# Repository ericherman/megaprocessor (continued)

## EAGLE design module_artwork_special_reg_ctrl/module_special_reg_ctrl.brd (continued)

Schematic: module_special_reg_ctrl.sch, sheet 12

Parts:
CMP27, CMP50: 3OR
CMP28: 4X2AND_OR

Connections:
NEXT_WR_DATA_MUX_PC_RA_MSB__7: CMP27.OUT_M (N), CMP28.P$1 (A0)
NEXT_WR_DATA_MUX_PC_RN_MSB: CMP28.OUT_P; also elsewhere on the board
NEXT_WR_DATA_MUX_PS: CMP27.P$3 (2); also elsewhere on the board
OPCODE_IS_PUSH_RA: CMP27.P$1 (0), CMP28.P$3 (B0); also elsewhere on the board
OPCODE_IS_TRAP_JSR_X: CMP28.P$8 (D1); also elsewhere on the board
SIZE_BIT_IS_BYTE: CMP27.P$2 (1); also elsewhere on the board
STATE_0: CMP28.P$4 (B1), CMP28.P$7 (D0); also elsewhere on the board
STATE_6: CMP50.P$1 (0); also elsewhere on the board
STATE_7: CMP50.P$2 (1); also elsewhere on the board
STATE_9: CMP50.P$3 (2); also elsewhere on the board
STATE_15: CMP28.P$5 (C0), CMP28.P$6 (C1); also elsewhere on the board
WE: CMP50.OUT_P
WILL_BE_STATE_7: CMP28.P$2 (A1); also elsewhere on the board

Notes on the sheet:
next_wr_data_mux_pc_rn_msb__7 = ~Cpnt_3OR(next_wr_data_mux_ps, bus_decode_special_reg_2.size_bit_is_byte, bus_decode_special_reg_1.opcode_is_push_ra);
next_wr_data_mux_pc_rn_msb = Cpnt_4x2AND_OR(opcode_is_trap_jsr_x, bus_state[0], bus_state[15], bus_state[15], bus_state[0], bus_decode_special_reg_1.opcode_is_push_ra, bus_decode_special_reg_2.will_be_7, next_wr_data_mux_pc_rn_msb__7);

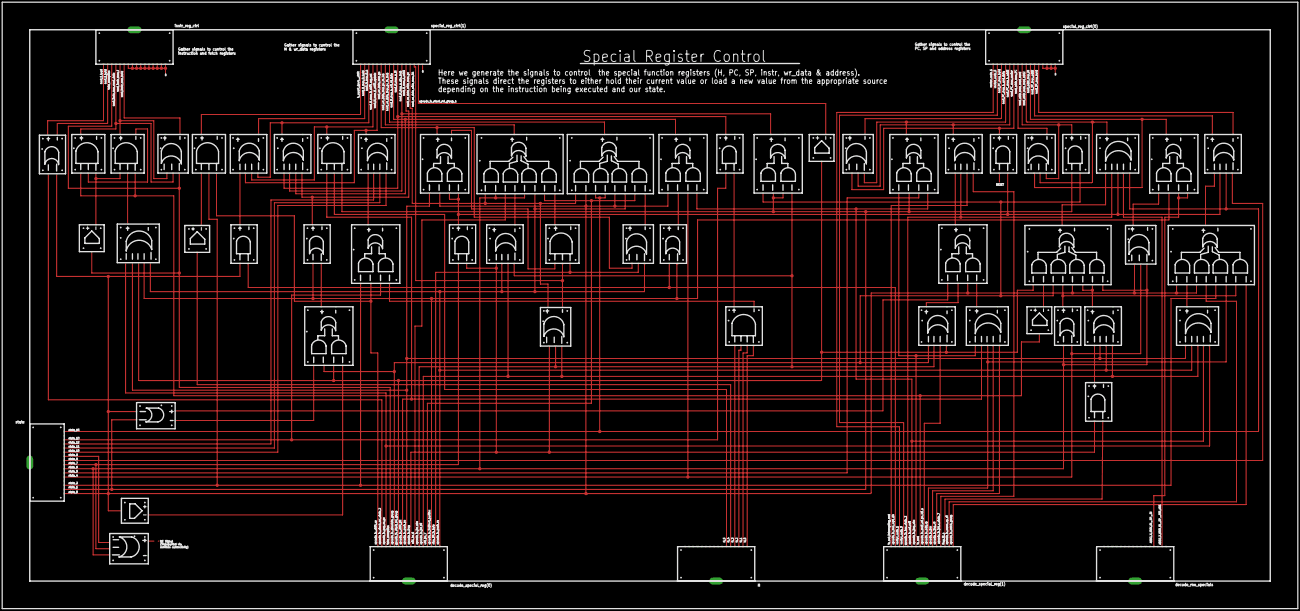
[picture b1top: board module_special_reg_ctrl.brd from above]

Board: 2 copper layers, 1193.8 x 558.8 mm, 61 parts (0 on the bottom side), 115 nets.

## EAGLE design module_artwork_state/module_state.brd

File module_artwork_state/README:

State Machine

The state machine controls the operation of the processor; directing the
execution of each instruction.

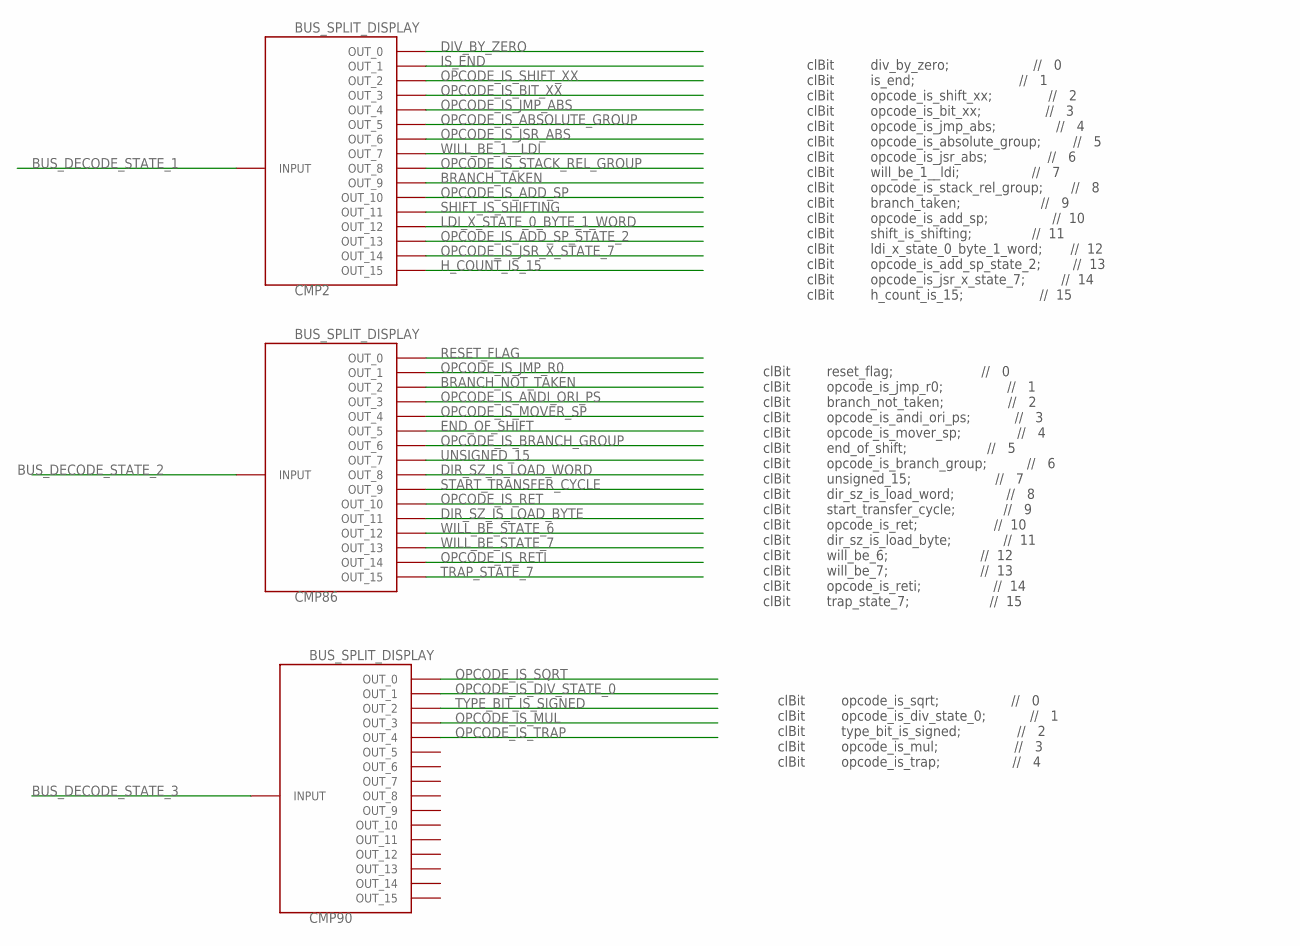
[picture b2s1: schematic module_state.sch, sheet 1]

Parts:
CMP2, CMP86, CMP90: BUS_SPLIT_DISPLAY

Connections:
BRANCH_NOT_TAKEN: CMP86.P$3 (OUT_2); also elsewhere on the board
BRANCH_TAKEN: CMP2.P$10 (OUT_9); also elsewhere on the board
BUS_DECODE_STATE_1: CMP2.INPUT
BUS_DECODE_STATE_2: CMP86.INPUT
BUS_DECODE_STATE_3: CMP90.INPUT
DIR_SZ_IS_LOAD_BYTE: CMP86.P$12 (OUT_11); also elsewhere on the board
DIR_SZ_IS_LOAD_WORD: CMP86.P$9 (OUT_8); also elsewhere on the board
DIV_BY_ZERO: CMP2.P$1 (OUT_0); also elsewhere on the board
END_OF_SHIFT: CMP86.P$6 (OUT_5); also elsewhere on the board
H_COUNT_IS_15: CMP2.P$16 (OUT_15); also elsewhere on the board
IS_END: CMP2.P$2 (OUT_1); also elsewhere on the board
LDI_X_STATE_0_BYTE_1_WORD: CMP2.P$13 (OUT_12); also elsewhere on the board
OPCODE_IS_ABSOLUTE_GROUP: CMP2.P$6 (OUT_5); also elsewhere on the board
OPCODE_IS_ADD_SP: CMP2.P$11 (OUT_10); also elsewhere on the board
OPCODE_IS_ADD_SP_STATE_2: CMP2.P$14 (OUT_13); also elsewhere on the board
OPCODE_IS_ANDI_ORI_PS: CMP86.P$4 (OUT_3); also elsewhere on the board
OPCODE_IS_BIT_XX: CMP2.P$4 (OUT_3); also elsewhere on the board
OPCODE_IS_BRANCH_GROUP: CMP86.P$7 (OUT_6); also elsewhere on the board
OPCODE_IS_DIV_STATE_0: CMP90.P$2 (OUT_1); also elsewhere on the board
OPCODE_IS_JMP_ABS: CMP2.P$5 (OUT_4); also elsewhere on the board
OPCODE_IS_JMP_R0: CMP86.P$2 (OUT_1); also elsewhere on the board
OPCODE_IS_JSR_ABS: CMP2.P$7 (OUT_6); also elsewhere on the board
OPCODE_IS_JSR_X_STATE_7: CMP2.P$15 (OUT_14); also elsewhere on the board
OPCODE_IS_MOVER_SP: CMP86.P$5 (OUT_4); also elsewhere on the board
OPCODE_IS_MUL: CMP90.P$4 (OUT_3); also elsewhere on the board
OPCODE_IS_RET: CMP86.P$11 (OUT_10); also elsewhere on the board
OPCODE_IS_RETI: CMP86.P$15 (OUT_14); also elsewhere on the board
OPCODE_IS_SHIFT_XX: CMP2.P$3 (OUT_2); also elsewhere on the board
OPCODE_IS_SQRT: CMP90.P$1 (OUT_0); also elsewhere on the board
OPCODE_IS_STACK_REL_GROUP: CMP2.P$9 (OUT_8); also elsewhere on the board
OPCODE_IS_TRAP: CMP90.P$5 (OUT_4); also elsewhere on the board
RESET_FLAG: CMP86.P$1 (OUT_0); also elsewhere on the board
SHIFT_IS_SHIFTING: CMP2.P$12 (OUT_11); also elsewhere on the board
START_TRANSFER_CYCLE: CMP86.P$10 (OUT_9); also elsewhere on the board
TRAP_STATE_7: CMP86.P$16 (OUT_15); also elsewhere on the board
TYPE_BIT_IS_SIGNED: CMP90.P$3 (OUT_2); also elsewhere on the board
UNSIGNED_15: CMP86.P$8 (OUT_7); also elsewhere on the board
WILL_BE_1__LDI: CMP2.P$8 (OUT_7); also elsewhere on the board
WILL_BE_STATE_6: CMP86.P$13 (OUT_12); also elsewhere on the board
WILL_BE_STATE_7: CMP86.P$14 (OUT_13); also elsewhere on the board

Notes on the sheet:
clBit div_by_zero; // 0 clBit is_end; // 1 clBit opcode_is_shift_xx; // 2 clBit opcode_is_bit_xx; // 3 clBit opcode_is_jmp_abs; // 4 clBit opcode_is_absolute_group; // 5 clBit opcode_is_jsr_abs; // 6 clBit will_be_1__ldi; // 7 clBit opcode_is_stack_rel_group; // 8 clBit branch_taken; // 9 clBit opc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
clBit reset_flag; // 0 clBit opcode_is_jmp_r0; // 1 clBit branch_not_taken; // 2 clBit opcode_is_andi_ori_ps; // 3 clBit opcode_is_mover_sp; // 4 clBit end_of_shift; // 5 clBit opcode_is_branch_group; // 6 clBit unsigned_15; // 7 clBit dir_sz_is_load_word; // 8 clBit start_transfer_cycle; // 9 clBi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
clBit opcode_is_sqrt; // 0 clBit opcode_is_div_state_0; // 1 clBit type_bit_is_signed; // 2 clBit opcode_is_mul; // 3 clBit opcode_is_trap; // 4

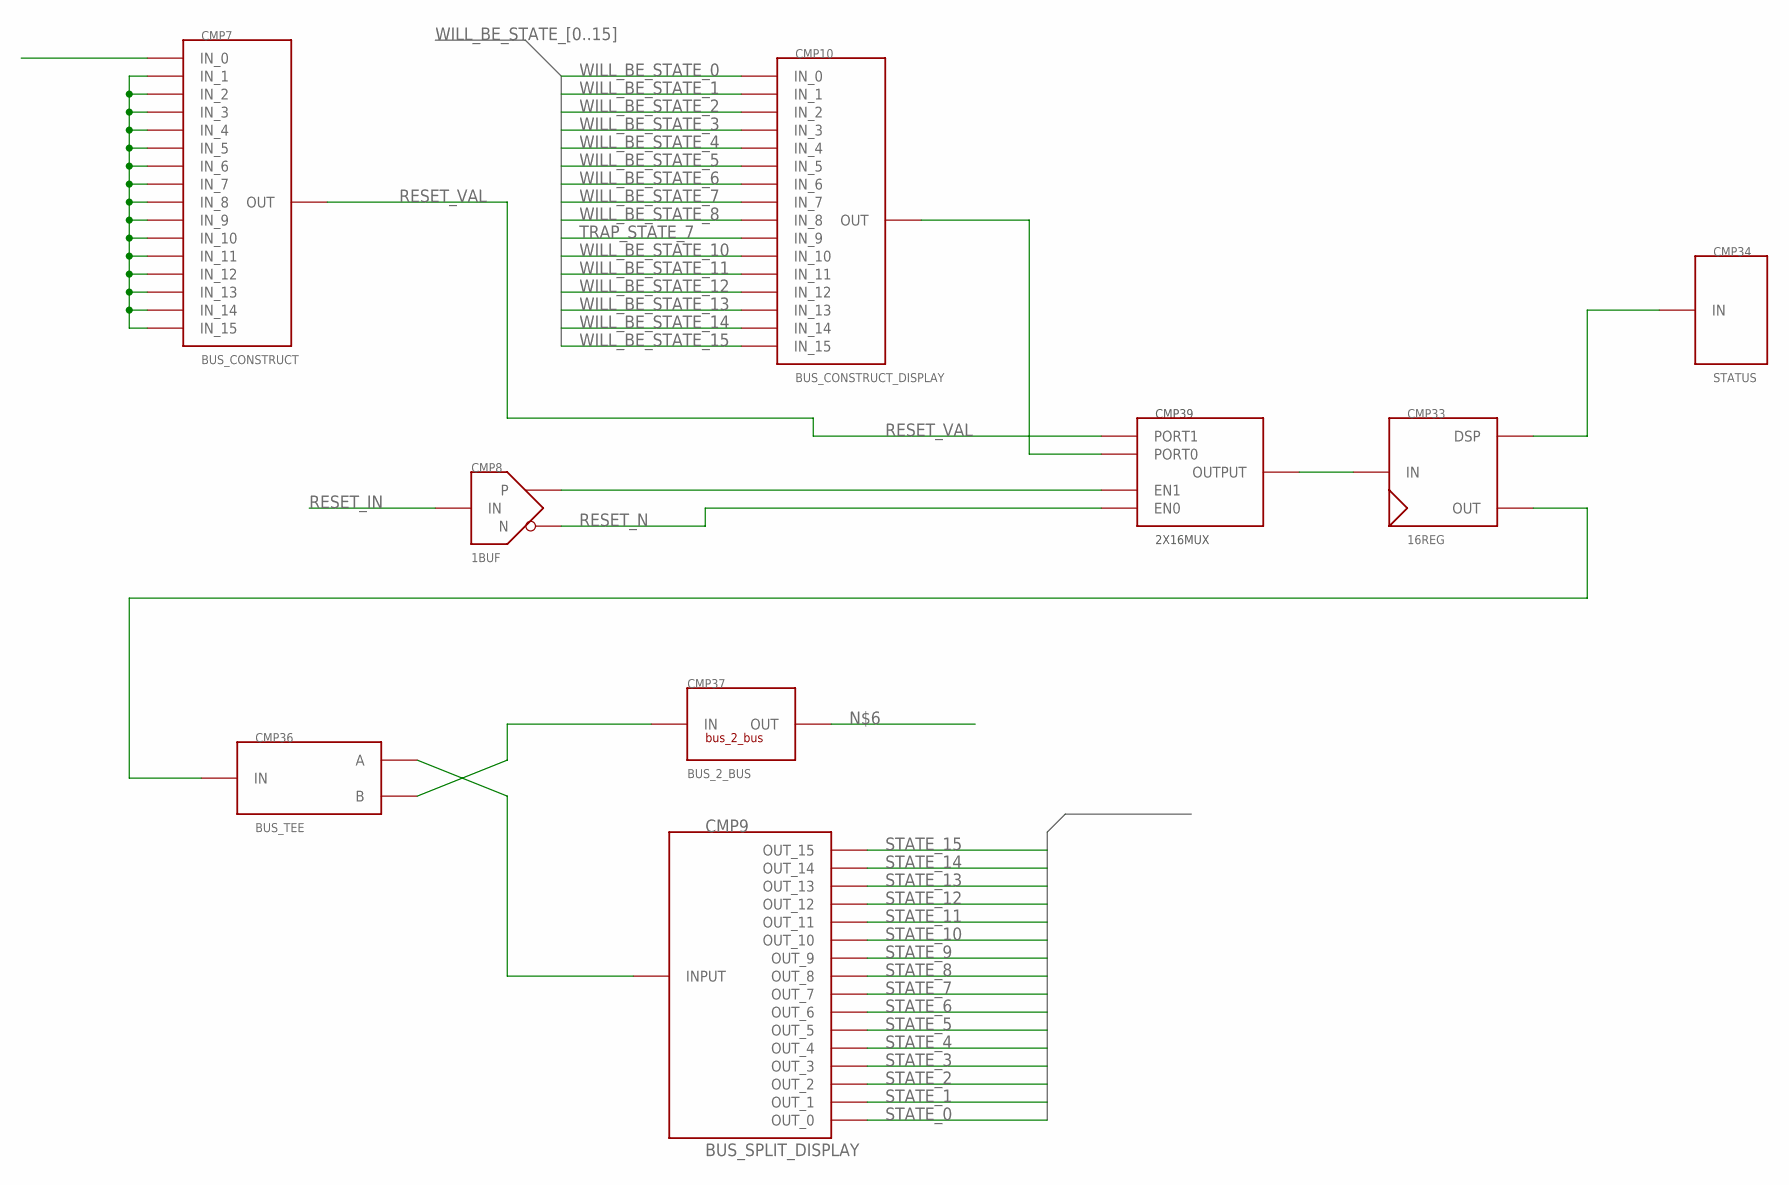
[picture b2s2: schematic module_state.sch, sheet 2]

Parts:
CMP7: BUS_CONSTRUCT; BUS_SPLIT
CMP8: 1BUF
CMP9: BUS_SPLIT_DISPLAY
CMP10: BUS_CONSTRUCT_DISPLAY; BUS_SPLIT_DISPLAY
CMP33: 16REG
CMP34: STATUS
CMP36: BUS_TEE
CMP37: BUS_2_BUS; BUS2BUS
CMP39: 2X16MUX

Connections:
unnamed: CMP33.DISPLAY (DSP), CMP34.P$1
unnamed: CMP33.OUT, CMP36.INPUT (IN)
unnamed: CMP36.OUTB (B), CMP37.P$1 (IN)
unnamed: CMP7.P$2 (IN_1), CMP7.P$3 (IN_2), CMP7.P$4 (IN_3), CMP7.P$5 (IN_4), CMP7.P$6 (IN_5), CMP7.P$7 (IN_6), CMP7.P$8 (IN_7), CMP7.P$9 (IN_8), CMP7.P$10 (IN_9), CMP7.P$11 (IN_10), CMP7.P$12 (IN_11), CMP7.P$13 (IN_12), CMP7.P$14 (IN_13), CMP7.P$15 (IN_14), CMP7.P$16 (IN_15)
unnamed: CMP9.INPUT, CMP36.OUT_A (A)
unnamed: CMP10.INPUT (OUT), CMP39.PORT0
unnamed: CMP33.INPUT (IN), CMP39.OUT (OUTPUT)
unnamed: CMP8.P, CMP39.EN1
RESET_IN: CMP8.IN
RESET_N: CMP8.N, CMP39.EN0
RESET_VAL: CMP7.INPUT (OUT), CMP39.PORT1
STATE_0: CMP9.P$1 (OUT_0); also elsewhere on the board
STATE_1: CMP9.P$2 (OUT_1); also elsewhere on the board
STATE_2: CMP9.P$3 (OUT_2); also elsewhere on the board
STATE_3: CMP9.P$4 (OUT_3)
STATE_4: CMP9.P$5 (OUT_4); also elsewhere on the board
STATE_5: CMP9.P$6 (OUT_5); also elsewhere on the board
STATE_6: CMP9.P$7 (OUT_6)
STATE_7: CMP9.P$8 (OUT_7); also elsewhere on the board
STATE_8: CMP9.P$9 (OUT_8); also elsewhere on the board
STATE_9: CMP9.P$10 (OUT_9); also elsewhere on the board
STATE_10: CMP9.P$11 (OUT_10); also elsewhere on the board
STATE_11: CMP9.P$12 (OUT_11); also elsewhere on the board
STATE_12: CMP9.P$13 (OUT_12); also elsewhere on the board
STATE_13: CMP9.P$14 (OUT_13); also elsewhere on the board
STATE_14: CMP9.P$15 (OUT_14); also elsewhere on the board
STATE_15: CMP9.P$16 (OUT_15)
TRAP_STATE_7: CMP10.P$10 (IN_9); also elsewhere on the board
WILL_BE_STATE_0: CMP10.P$1 (IN_0); also elsewhere on the board
WILL_BE_STATE_1: CMP10.P$2 (IN_1); also elsewhere on the board
WILL_BE_STATE_2: CMP10.P$3 (IN_2); also elsewhere on the board
WILL_BE_STATE_3: CMP10.P$4 (IN_3); also elsewhere on the board
WILL_BE_STATE_4: CMP10.P$5 (IN_4); also elsewhere on the board
WILL_BE_STATE_5: CMP10.P$6 (IN_5); also elsewhere on the board
WILL_BE_STATE_6: CMP10.P$7 (IN_6); also elsewhere on the board
WILL_BE_STATE_7: CMP10.P$8 (IN_7); also elsewhere on the board
WILL_BE_STATE_8: CMP10.P$9 (IN_8); also elsewhere on the board
WILL_BE_STATE_10: CMP10.P$11 (IN_10); also elsewhere on the board
WILL_BE_STATE_11: CMP10.P$12 (IN_11); also elsewhere on the board
WILL_BE_STATE_12: CMP10.P$13 (IN_12); also elsewhere on the board
WILL_BE_STATE_13: CMP10.P$14 (IN_13); also elsewhere on the board
WILL_BE_STATE_14: CMP10.P$15 (IN_14); also elsewhere on the board
WILL_BE_STATE_15: CMP10.P$16 (IN_15); also elsewhere on the board

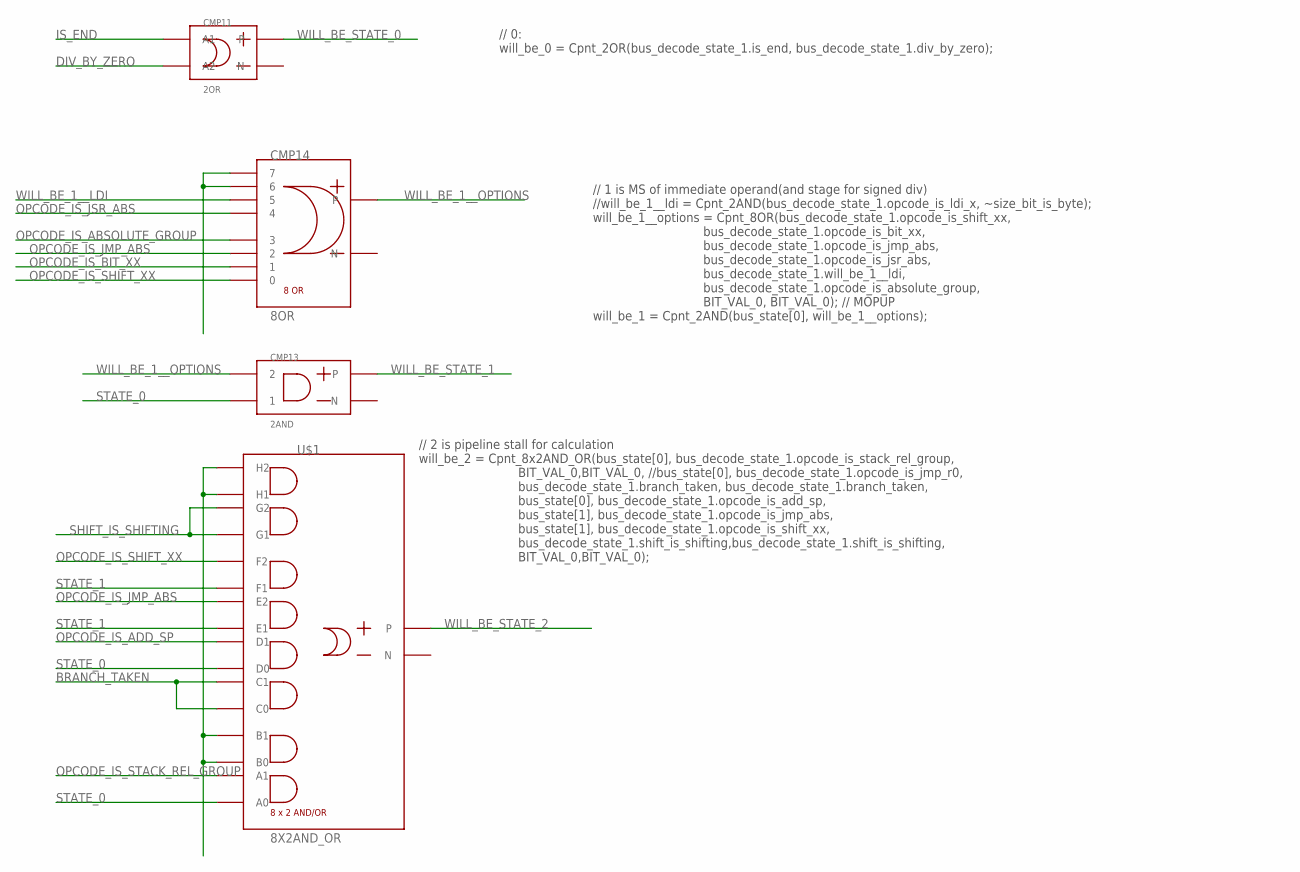
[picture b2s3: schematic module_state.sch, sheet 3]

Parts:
CMP11: 2OR
CMP13: 2AND
CMP14: 8OR
U$1: 8X2AND_OR

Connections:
BRANCH_TAKEN: U$1.P$5 (C0), U$1.P$6 (C1); also elsewhere on the board
DIV_BY_ZERO: CMP11.P$1 (A2); also elsewhere on the board
IS_END: CMP11.P$2 (A1); also elsewhere on the board
unnamed: U$1.P$3 (B0), U$1.P$4 (B1), U$1.P$15 (H1), U$1.P$16 (H2)
unnamed: CMP14.7 (6), CMP14.8 (7)
OPCODE_IS_ABSOLUTE_GROUP: CMP14.4 (3); also elsewhere on the board
OPCODE_IS_ADD_SP: U$1.P$8 (D1); also elsewhere on the board
OPCODE_IS_BIT_XX: CMP14.2 (1); also elsewhere on the board
OPCODE_IS_JMP_ABS: CMP14.3 (2), U$1.P$10 (E2); also elsewhere on the board
OPCODE_IS_JSR_ABS: CMP14.5 (4); also elsewhere on the board
OPCODE_IS_SHIFT_XX: CMP14.1 (0), U$1.P$12 (F2); also elsewhere on the board
OPCODE_IS_STACK_REL_GROUP: U$1.P$2 (A1); also elsewhere on the board
SHIFT_IS_SHIFTING: U$1.P$13 (G1), U$1.P$14 (G2); also elsewhere on the board
STATE_0: CMP13.P$1 (1), U$1.P$1 (A0), U$1.P$7 (D0); also elsewhere on the board
STATE_1: U$1.P$9 (E1), U$1.P$11 (F1); also elsewhere on the board
WILL_BE_1__LDI: CMP14.6 (5); also elsewhere on the board
WILL_BE_1__OPTIONS: CMP13.P$2 (2), CMP14.OUT_P
WILL_BE_STATE_0: CMP11.OUT_P; also elsewhere on the board
WILL_BE_STATE_1: CMP13.OUT_P; also elsewhere on the board
WILL_BE_STATE_2: U$1.OUT_P; also elsewhere on the board

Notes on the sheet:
// 0: will_be_0 = Cpnt_2OR(bus_decode_state_1.is_end, bus_decode_state_1.div_by_zero);
// 1 is MS of immediate operand(and stage for signed div) //will_be_1__ldi = Cpnt_2AND(bus_decode_state_1.opcode_is_ldi_x, ~size_bit_is_byte); will_be_1__options = Cpnt_8OR(bus_decode_state_1.opcode_is_shift_xx, bus_decode_state_1.opcode_is_bit_xx, bus_decode_state_1.opcode_is_jmp_abs, bus_decode_s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
// 2 is pipeline stall for calculation will_be_2 = Cpnt_8x2AND_OR(bus_state[0], bus_decode_state_1.opcode_is_stack_rel_group, BIT_VAL_0,BIT_VAL_0, //bus_state[0], bus_decode_state_1.opcode_is_jmp_r0, bus_decode_state_1.branch_taken, bus_decode_state_1.branch_taken, bus_state[0], bus_decode_state_1.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

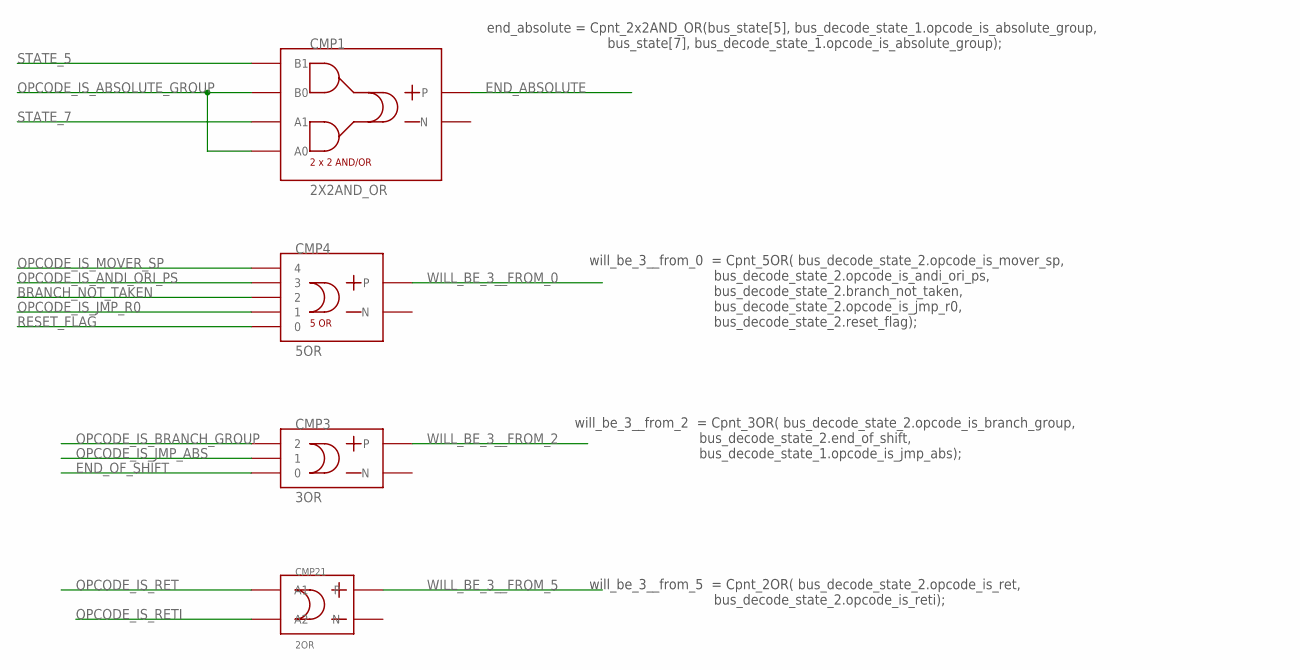
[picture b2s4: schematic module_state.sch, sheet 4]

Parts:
CMP1: 2X2AND_OR
CMP3: 3OR
CMP4: 5OR
CMP21: 2OR

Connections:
BRANCH_NOT_TAKEN: CMP4.3 (2); also elsewhere on the board
END_ABSOLUTE: CMP1.OUT_P; also elsewhere on the board
END_OF_SHIFT: CMP3.P$1 (0); also elsewhere on the board
OPCODE_IS_ABSOLUTE_GROUP: CMP1.P$1 (A0), CMP1.P$3 (B0); also elsewhere on the board
OPCODE_IS_ANDI_ORI_PS: CMP4.4 (3); also elsewhere on the board
OPCODE_IS_BRANCH_GROUP: CMP3.P$3 (2); also elsewhere on the board
OPCODE_IS_JMP_ABS: CMP3.P$2 (1); also elsewhere on the board
OPCODE_IS_JMP_R0: CMP4.2 (1); also elsewhere on the board
OPCODE_IS_MOVER_SP: CMP4.5 (4); also elsewhere on the board
OPCODE_IS_RET: CMP21.P$1 (A2); also elsewhere on the board
OPCODE_IS_RETI: CMP21.P$2 (A1); also elsewhere on the board
RESET_FLAG: CMP4.1 (0); also elsewhere on the board
STATE_5: CMP1.P$4 (B1); also elsewhere on the board
STATE_7: CMP1.P$2 (A1); also elsewhere on the board
WILL_BE_3__FROM_0: CMP4.OUT_P; also elsewhere on the board
WILL_BE_3__FROM_2: CMP3.OUT_P; also elsewhere on the board
WILL_BE_3__FROM_5: CMP21.OUT_P; also elsewhere on the board

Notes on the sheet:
end_absolute = Cpnt_2x2AND_OR(bus_state[5], bus_decode_state_1.opcode_is_absolute_group, bus_state[7], bus_decode_state_1.opcode_is_absolute_group);
will_be_3__from_0 = Cpnt_5OR( bus_decode_state_2.opcode_is_mover_sp, bus_decode_state_2.opcode_is_andi_ori_ps, bus_decode_state_2.branch_not_taken, bus_decode_state_2.opcode_is_jmp_r0, bus_decode_state_2.reset_flag);
will_be_3__from_2 = Cpnt_3OR( bus_decode_state_2.opcode_is_branch_group, bus_decode_state_2.end_of_shift, bus_decode_state_1.opcode_is_jmp_abs);
will_be_3__from_5 = Cpnt_2OR( bus_decode_state_2.opcode_is_ret, bus_decode_state_2.opcode_is_reti);

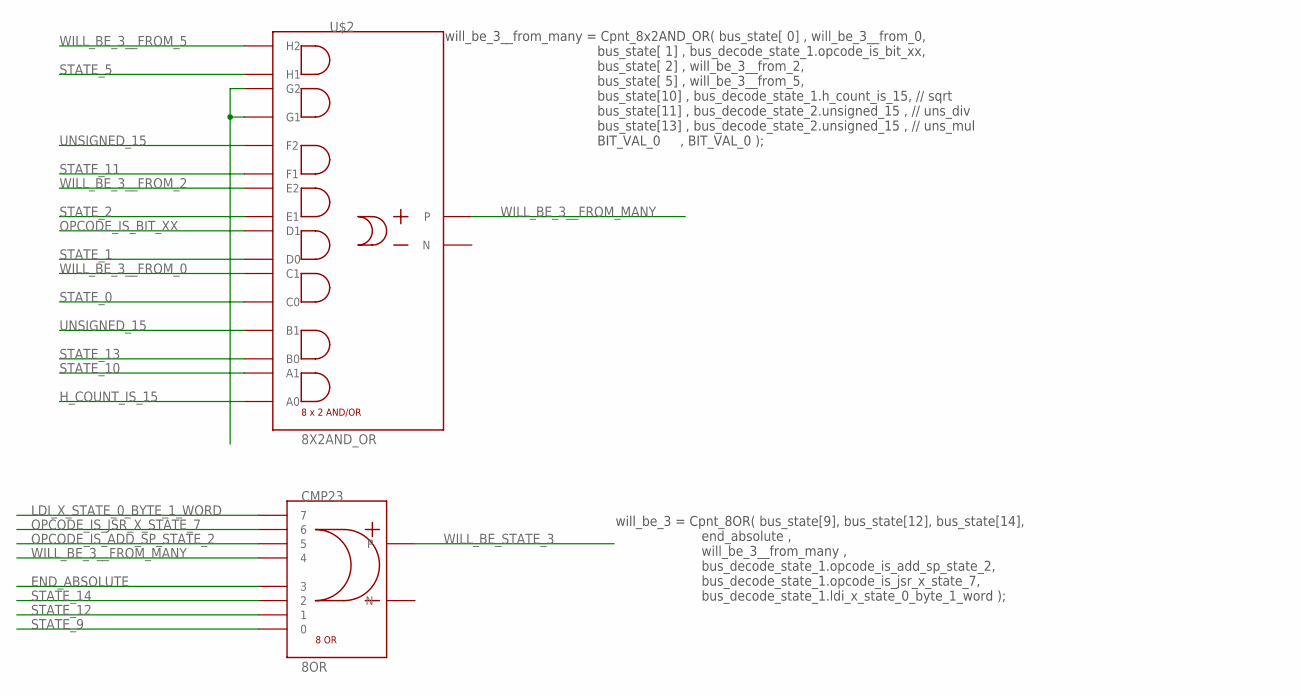
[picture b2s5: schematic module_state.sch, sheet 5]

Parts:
CMP23: 8OR
U$2: 8X2AND_OR

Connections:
END_ABSOLUTE: CMP23.8 (7); also elsewhere on the board
H_COUNT_IS_15: U$2.P$1 (A0); also elsewhere on the board
LDI_X_STATE_0_BYTE_1_WORD: CMP23.4 (3); also elsewhere on the board
unnamed: U$2.P$13 (G1), U$2.P$14 (G2)
OPCODE_IS_ADD_SP_STATE_2: CMP23.5 (4); also elsewhere on the board
OPCODE_IS_BIT_XX: U$2.P$8 (D1); also elsewhere on the board
OPCODE_IS_JSR_X_STATE_7: CMP23.6 (5); also elsewhere on the board
STATE_0: U$2.P$5 (C0); also elsewhere on the board
STATE_1: U$2.P$7 (D0); also elsewhere on the board
STATE_2: U$2.P$9 (E1); also elsewhere on the board
STATE_5: U$2.P$15 (H1); also elsewhere on the board
STATE_9: CMP23.1 (0); also elsewhere on the board
STATE_10: U$2.P$2 (A1); also elsewhere on the board
STATE_11: U$2.P$11 (F1); also elsewhere on the board
STATE_12: CMP23.2 (1); also elsewhere on the board
STATE_13: U$2.P$3 (B0); also elsewhere on the board
STATE_14: CMP23.3 (2); also elsewhere on the board
UNSIGNED_15: U$2.P$4 (B1), U$2.P$12 (F2); also elsewhere on the board
WILL_BE_3__FROM_0: U$2.P$6 (C1); also elsewhere on the board
WILL_BE_3__FROM_2: U$2.P$10 (E2); also elsewhere on the board
WILL_BE_3__FROM_5: U$2.P$16 (H2); also elsewhere on the board
WILL_BE_3__FROM_MANY: CMP23.7 (6), U$2.OUT_P
WILL_BE_STATE_3: CMP23.OUT_P; also elsewhere on the board

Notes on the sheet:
will_be_3__from_many = Cpnt_8x2AND_OR( bus_state[ 0] , will_be_3__from_0, bus_state[ 1] , bus_decode_state_1.opcode_is_bit_xx, bus_state[ 2] , will_be_3__from_2, bus_state[ 5] , will_be_3__from_5, bus_state[10] , bus_decode_state_1.h_count_is_15, // sqrt bus_state[11] , bus_decode_state_2.unsigned_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
will_be_3 = Cpnt_8OR( bus_state[9], bus_state[12], bus_state[14], end_absolute , will_be_3__from_many , bus_decode_state_1.opcode_is_add_sp_state_2, bus_decode_state_1.opcode_is_jsr_x_state_7, bus_decode_state_1.ldi_x_state_0_byte_1_word );

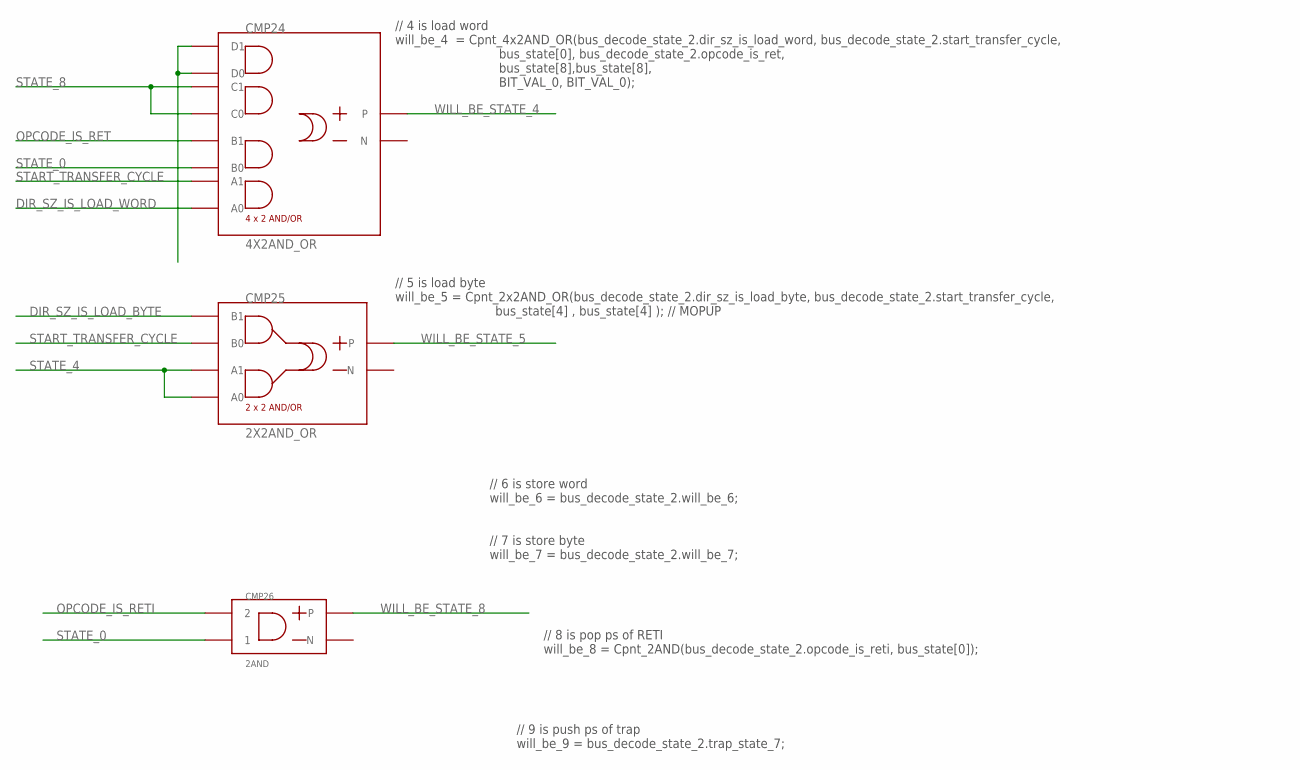
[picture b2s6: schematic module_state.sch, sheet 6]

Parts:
CMP24: 4X2AND_OR
CMP25: 2X2AND_OR
CMP26: 2AND

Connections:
DIR_SZ_IS_LOAD_BYTE: CMP25.P$4 (B1); also elsewhere on the board
DIR_SZ_IS_LOAD_WORD: CMP24.P$1 (A0); also elsewhere on the board
unnamed: CMP24.P$7 (D0), CMP24.P$8 (D1)
OPCODE_IS_RET: CMP24.P$4 (B1); also elsewhere on the board
OPCODE_IS_RETI: CMP26.P$2 (2); also elsewhere on the board
START_TRANSFER_CYCLE: CMP24.P$2 (A1), CMP25.P$3 (B0); also elsewhere on the board
STATE_0: CMP24.P$3 (B0), CMP26.P$1 (1); also elsewhere on the board
STATE_4: CMP25.P$1 (A0), CMP25.P$2 (A1); also elsewhere on the board
STATE_8: CMP24.P$5 (C0), CMP24.P$6 (C1); also elsewhere on the board
WILL_BE_STATE_4: CMP24.OUT_P; also elsewhere on the board
WILL_BE_STATE_5: CMP25.OUT_P; also elsewhere on the board
WILL_BE_STATE_8: CMP26.OUT_P; also elsewhere on the board

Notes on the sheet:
// 4 is load word will_be_4 = Cpnt_4x2AND_OR(bus_decode_state_2.dir_sz_is_load_word, bus_decode_state_2.start_transfer_cycle, bus_state[0], bus_decode_state_2.opcode_is_ret, bus_state[8],bus_state[8], BIT_VAL_0, BIT_VAL_0);
// 5 is load byte will_be_5 = Cpnt_2x2AND_OR(bus_decode_state_2.dir_sz_is_load_byte, bus_decode_state_2.start_transfer_cycle, bus_state[4] , bus_state[4] ); // MOPUP
// 6 is store word will_be_6 = bus_decode_state_2.will_be_6; // 7 is store byte will_be_7 = bus_decode_state_2.will_be_7;
// 8 is pop ps of RETI will_be_8 = Cpnt_2AND(bus_decode_state_2.opcode_is_reti, bus_state[0]);
// 9 is push ps of trap will_be_9 = bus_decode_state_2.trap_state_7;

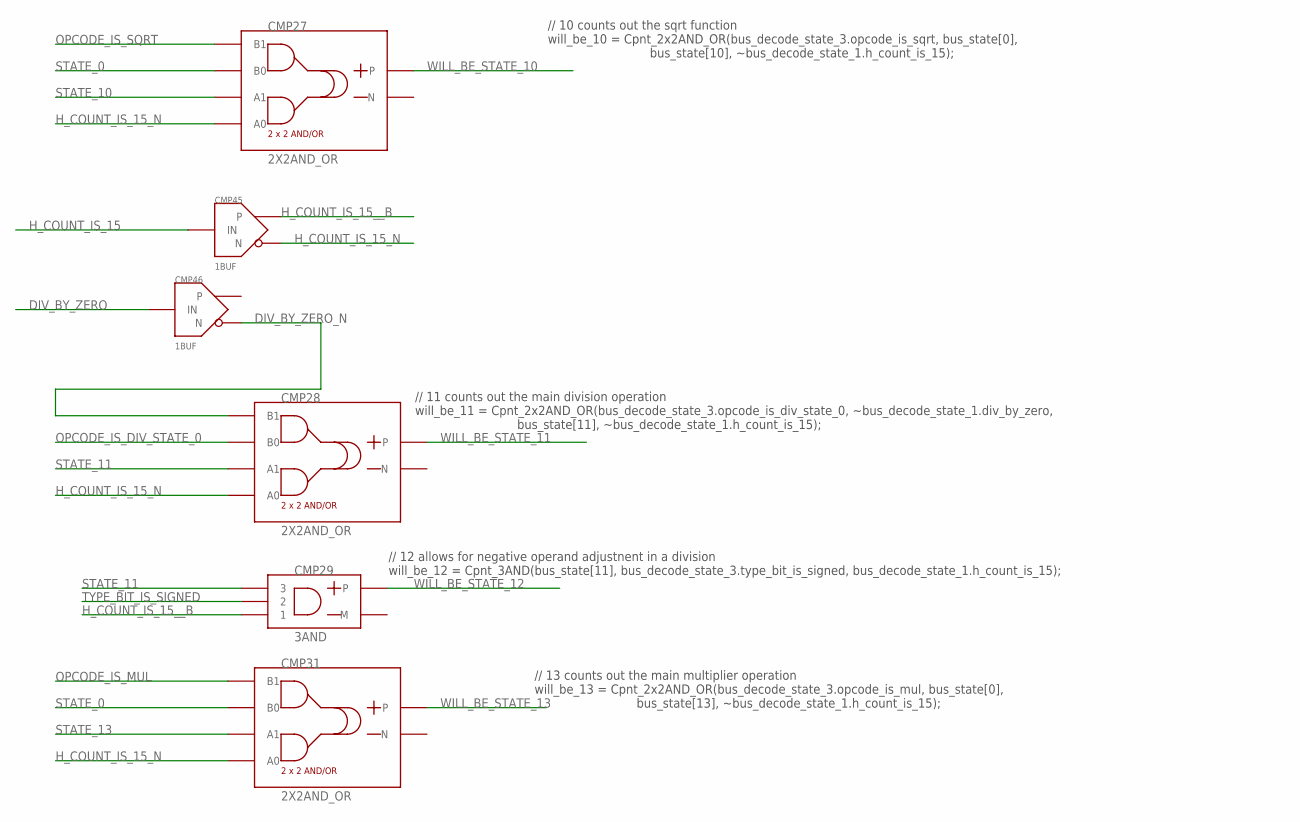
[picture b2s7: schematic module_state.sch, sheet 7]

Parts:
CMP27, CMP28, CMP31: 2X2AND_OR
CMP29: 3AND
CMP45, CMP46: 1BUF

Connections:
DIV_BY_ZERO: CMP46.IN; also elsewhere on the board
DIV_BY_ZERO_N: CMP28.P$4 (B1), CMP46.N
H_COUNT_IS_15: CMP45.IN; also elsewhere on the board
H_COUNT_IS_15_N: CMP27.P$1 (A0), CMP28.P$1 (A0), CMP31.P$1 (A0), CMP45.N
H_COUNT_IS_15__B: CMP29.P$1 (1), CMP45.P; also elsewhere on the board
OPCODE_IS_DIV_STATE_0: CMP28.P$3 (B0); also elsewhere on the board
OPCODE_IS_MUL: CMP31.P$4 (B1); also elsewhere on the board
OPCODE_IS_SQRT: CMP27.P$4 (B1); also elsewhere on the board
STATE_0: CMP27.P$3 (B0), CMP31.P$3 (B0); also elsewhere on the board
STATE_10: CMP27.P$2 (A1); also elsewhere on the board
STATE_11: CMP28.P$2 (A1), CMP29.P$3 (3); also elsewhere on the board
STATE_13: CMP31.P$2 (A1); also elsewhere on the board
TYPE_BIT_IS_SIGNED: CMP29.P$2 (2); also elsewhere on the board
WILL_BE_STATE_10: CMP27.OUT_P; also elsewhere on the board
WILL_BE_STATE_11: CMP28.OUT_P; also elsewhere on the board
WILL_BE_STATE_12: CMP29.OUT_P; also elsewhere on the board
WILL_BE_STATE_13: CMP31.OUT_P; also elsewhere on the board

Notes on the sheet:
// 10 counts out the sqrt function will_be_10 = Cpnt_2x2AND_OR(bus_decode_state_3.opcode_is_sqrt, bus_state[0], bus_state[10], ~bus_decode_state_1.h_count_is_15);
// 11 counts out the main division operation will_be_11 = Cpnt_2x2AND_OR(bus_decode_state_3.opcode_is_div_state_0, ~bus_decode_state_1.div_by_zero, bus_state[11], ~bus_decode_state_1.h_count_is_15);
// 12 allows for negative operand adjustnent in a division will_be_12 = Cpnt_3AND(bus_state[11], bus_decode_state_3.type_bit_is_signed, bus_decode_state_1.h_count_is_15);
// 13 counts out the main multiplier operation will_be_13 = Cpnt_2x2AND_OR(bus_decode_state_3.opcode_is_mul, bus_state[0], bus_state[13], ~bus_decode_state_1.h_count_is_15);

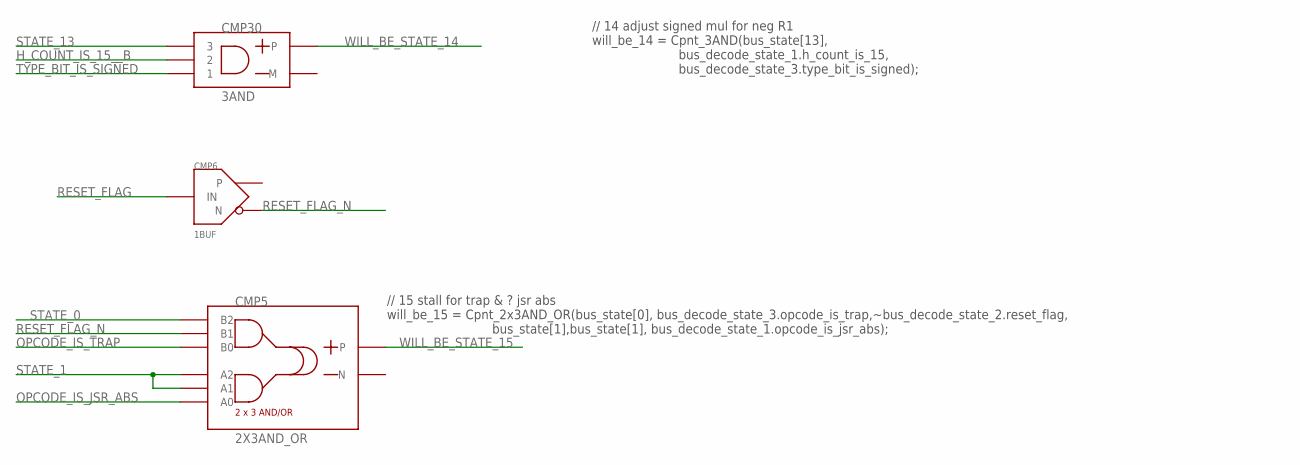
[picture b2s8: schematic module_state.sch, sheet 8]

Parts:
CMP5: 2X3AND_OR
CMP6: 1BUF
CMP30: 3AND

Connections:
H_COUNT_IS_15__B: CMP30.P$2 (2); also elsewhere on the board
OPCODE_IS_JSR_ABS: CMP5.P$1 (A0); also elsewhere on the board
OPCODE_IS_TRAP: CMP5.P$4 (B0); also elsewhere on the board
RESET_FLAG: CMP6.IN; also elsewhere on the board
RESET_FLAG_N: CMP5.P$5 (B1), CMP6.N
STATE_0: CMP5.P$6 (B2); also elsewhere on the board
STATE_1: CMP5.P$2 (A1), CMP5.P$3 (A2); also elsewhere on the board
STATE_13: CMP30.P$3 (3); also elsewhere on the board
TYPE_BIT_IS_SIGNED: CMP30.P$1 (1); also elsewhere on the board
WILL_BE_STATE_14: CMP30.OUT_P; also elsewhere on the board
WILL_BE_STATE_15: CMP5.OUT_P; also elsewhere on the board

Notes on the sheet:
// 14 adjust signed mul for neg R1 will_be_14 = Cpnt_3AND(bus_state[13], bus_decode_state_1.h_count_is_15, bus_decode_state_3.type_bit_is_signed);
// 15 stall for trap & ? jsr abs will_be_15 = Cpnt_2x3AND_OR(bus_state[0], bus_decode_state_3.opcode_is_trap,~bus_decode_state_2.reset_flag, bus_state[1],bus_state[1], bus_decode_state_1.opcode_is_jsr_abs);

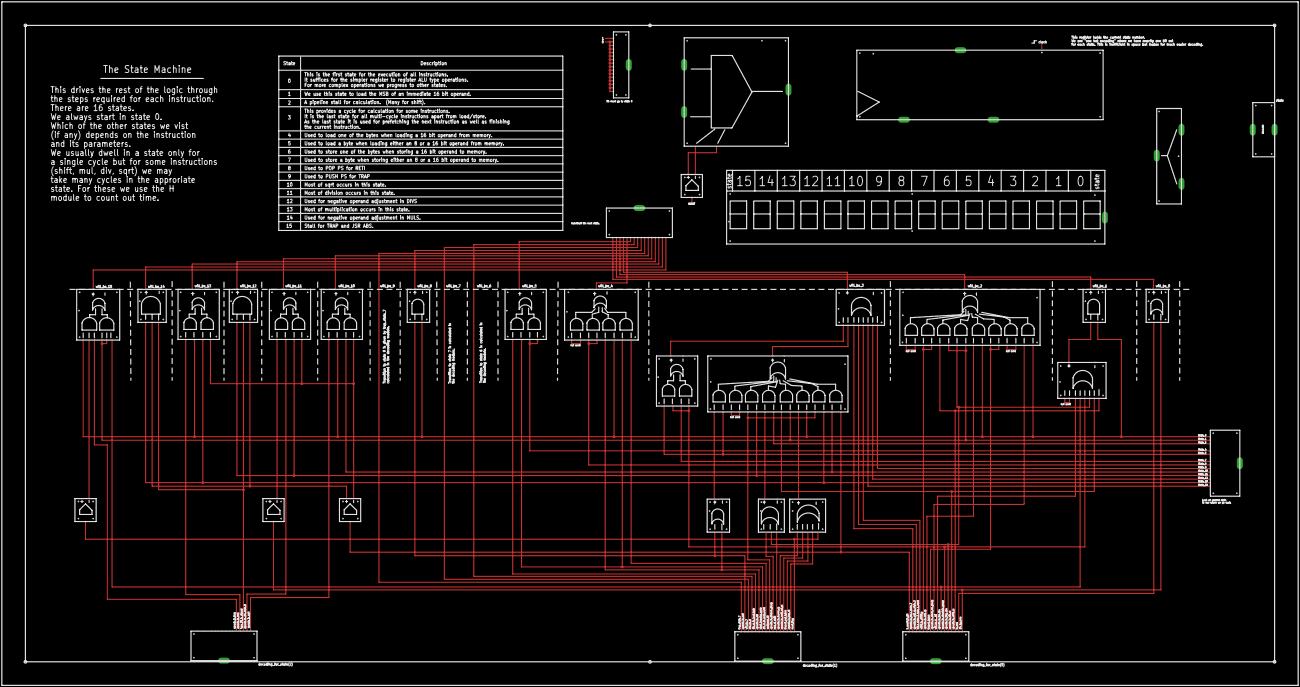
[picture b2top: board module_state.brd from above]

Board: 2 copper layers, 1397.0 x 736.6 mm, 34 parts (0 on the bottom side), 87 nets.

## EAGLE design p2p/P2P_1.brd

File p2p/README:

frame to frame

This combines four data buses together to make a 64 way bus for joining
frames together (a small number of wide cables is easier to deal with
than lots of small ones).

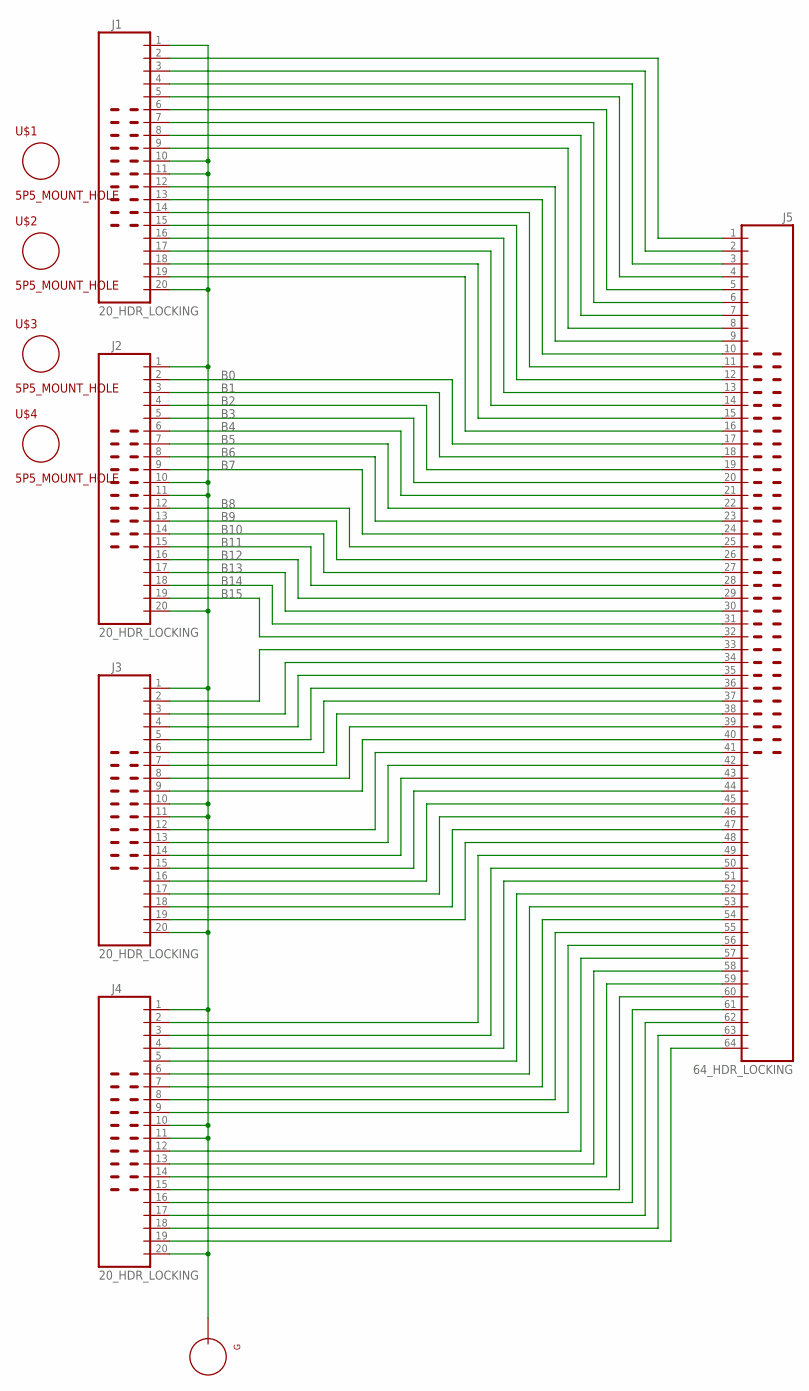
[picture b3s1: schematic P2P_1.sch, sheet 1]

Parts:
G: TEST_LOOP
J1, J2, J3, J4: 20_HDR_LOCKING
J5: 64_HDR_LOCKING
U$1, U$2, U$3, U$4: 5P5_MOUNT_HOLE; 5P5M_HOLE

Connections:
B0: J2.2, J5.17; also elsewhere on the board
B1: J2.3, J5.18; also elsewhere on the board
B2: J2.4, J5.19; also elsewhere on the board
B3: J2.5, J5.20; also elsewhere on the board
B4: J2.6, J5.21; also elsewhere on the board
B5: J2.7, J5.22; also elsewhere on the board
B6: J2.8, J5.23; also elsewhere on the board
B7: J2.9, J5.24; also elsewhere on the board
B8: J2.12, J5.25; also elsewhere on the board
B9: J2.13, J5.26; also elsewhere on the board
B10: J2.14, J5.27; also elsewhere on the board
B11: J2.15, J5.28; also elsewhere on the board
B12: J2.16, J5.29; also elsewhere on the board
B13: J2.17, J5.30; also elsewhere on the board
B14: J2.18, J5.31; also elsewhere on the board
B15: J2.19, J5.32; also elsewhere on the board
unnamed: G.P$1, J1.1, J1.10, J1.11, J1.20, J2.1, J2.10, J2.11, J2.20, J3.1, J3.10, J3.11, J3.20, J4.1, J4.10, J4.11, J4.20
unnamed: J3.2, J5.33
unnamed: J3.3, J5.34
unnamed: J3.4, J5.35
unnamed: J3.5, J5.36
unnamed: J3.6, J5.37
unnamed: J3.7, J5.38
unnamed: J3.8, J5.39
unnamed: J3.9, J5.40
unnamed: J3.12, J5.41
unnamed: J3.13, J5.42
unnamed: J3.14, J5.43
unnamed: J3.15, J5.44
unnamed: J3.16, J5.45
unnamed: J3.17, J5.46
unnamed: J3.18, J5.47
unnamed: J3.19, J5.48
unnamed: J4.2, J5.49
unnamed: J4.3, J5.50
unnamed: J4.4, J5.51
unnamed: J4.5, J5.52
unnamed: J4.6, J5.53
unnamed: J4.7, J5.54
unnamed: J4.8, J5.55
unnamed: J4.9, J5.56
unnamed: J1.19, J5.16
unnamed: J1.18, J5.15
unnamed: J1.17, J5.14
unnamed: J1.16, J5.13
unnamed: J1.15, J5.12
unnamed: J1.14, J5.11
unnamed: J1.13, J5.10
unnamed: J1.12, J5.9
unnamed: J1.9, J5.8
unnamed: J1.8, J5.7
unnamed: J1.7, J5.6
unnamed: J1.6, J5.5
unnamed: J1.5, J5.4
unnamed: J1.4, J5.3
unnamed: J1.3, J5.2
unnamed: J1.2, J5.1
unnamed: J4.12, J5.57
unnamed: J4.13, J5.58
unnamed: J4.14, J5.59
unnamed: J4.15, J5.60
unnamed: J4.16, J5.61
unnamed: J4.17, J5.62
unnamed: J4.18, J5.63
unnamed: J4.19, J5.64
